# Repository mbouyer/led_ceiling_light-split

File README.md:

# led_ceiling_light-split

Plafonier à LEDs 12V pour bateau, avec 2 puissances (puissance réduite en navigation). Version en deux parties de led_ceiling_light

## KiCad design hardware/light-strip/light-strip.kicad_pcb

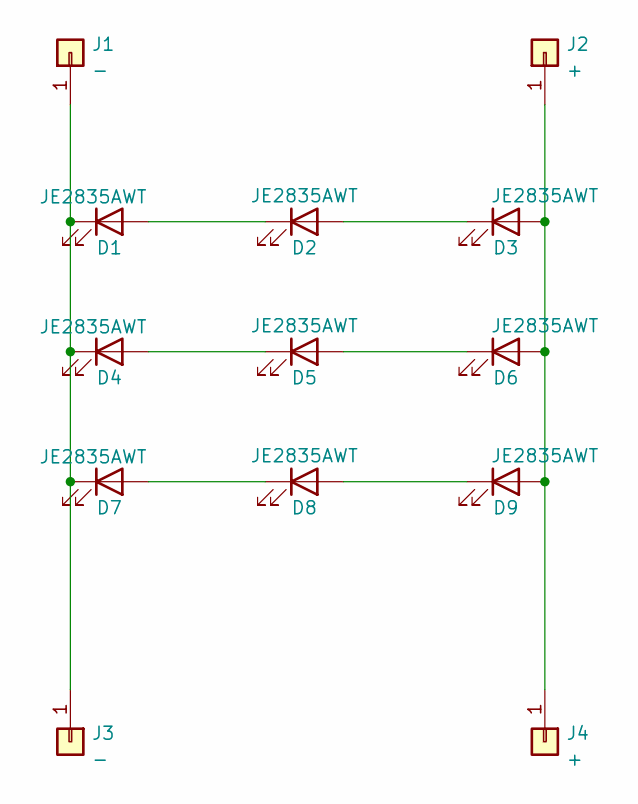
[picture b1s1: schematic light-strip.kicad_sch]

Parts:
D1, D2, D3, D4, D5, D6, D7, D8, D9: JE2835AWT; LED_PLCC_2835_Handsoldering
J1, J3: -; SolderWirePad_1x01_SMD_5x10mm
J2, J4: +; SolderWirePad_1x01_SMD_5x10mm

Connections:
unnamed: D1.1 (K), D4.1 (K), D7.1 (K), J1.1, J3.1
unnamed: D1.2 (A), D2.1 (K)
unnamed: D2.2 (A), D3.1 (K)
unnamed: D3.2 (A), D6.2 (A), D9.2 (A), J2.1, J4.1
unnamed: D4.2 (A), D5.1 (K)
unnamed: D5.2 (A), D6.1 (K)
unnamed: D7.2 (A), D8.1 (K)
unnamed: D8.2 (A), D9.1 (K)

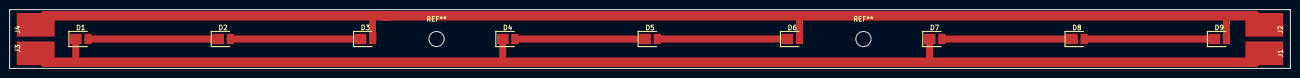
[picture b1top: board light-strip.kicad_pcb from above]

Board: 2 copper layers, 270.0 x 12.4 mm, 13 parts (0 on the bottom side), 8 nets.

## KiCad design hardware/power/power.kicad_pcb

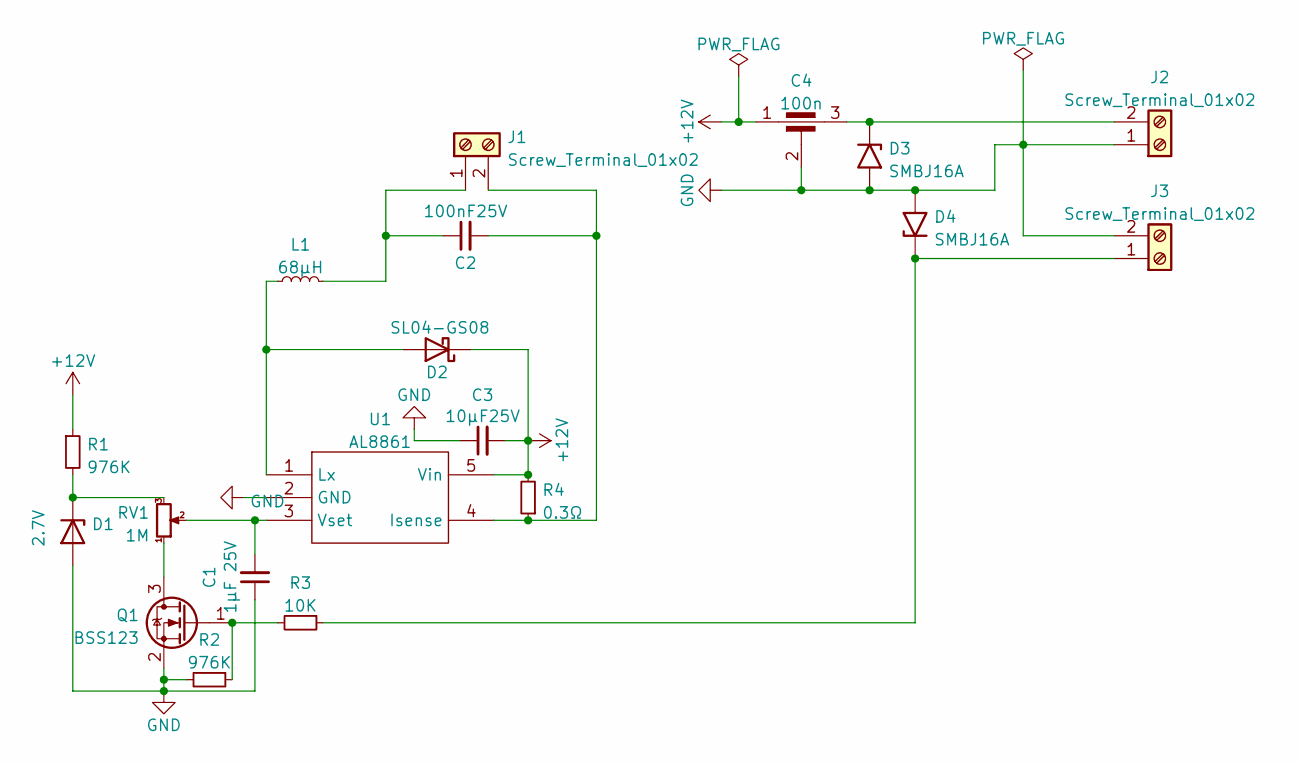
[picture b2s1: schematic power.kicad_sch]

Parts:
C1: 1µF 25V; C_0805_2012Metric_Pad1.18x1.45mm_HandSolder
C2: 100nF25V; C_0603_1608Metric_Pad1.08x0.95mm_HandSolder
C3: 10µF25V; C_1210_3225Metric_Pad1.33x2.70mm_HandSolder
C4: 100n; C_filter_0805
D1: 2.7V; D_MiniMELF_Handsoldering
D2: SL04-GS08; D_SMF
D3, D4: SMBJ16A; D_SMB_Handsoldering
J1, J2, J3: Screw_Terminal_01x02; amphenol_TZ02
L1: 68µH; L_Taiyo-Yuden_NR-80xx_HandSoldering
Q1: BSS123; SOT-23
R1, R2: 976K; R_0603_1608Metric_Pad0.98x0.95mm_HandSolder
R3: 10K; R_0805_2012Metric_Pad1.20x1.40mm_HandSolder
R4: 0.3Ω; R_1206_3216Metric_Pad1.30x1.75mm_HandSolder
RV1: 1M; Potentiometer_Piher_PT-10-V10_Vertical
U1: AL8861; TSOT-23-5_HandSoldering

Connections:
+12V: C3.2, C4.1, D2.1 (K), R1.1, R4.2, U1.5 (Vin)
GND: C1.1, C3.1, C4.2, D1.2 (A), D3.2 (A2), D4.2 (A2), J2.1, J3.2, Q1.2 (S), R2.2, U1.2 (GND)
unnamed: C1.2, RV1.2, U1.3 (Vset)
unnamed: C2.1, J1.1, L1.2
unnamed: C2.2, J1.2, R4.1, U1.4 (Isense)
unnamed: C4.3, D3.1 (A1), J2.2
unnamed: D1.1 (K), R1.2, RV1.3
unnamed: D2.2 (A), L1.1, U1.1 (Lx)
unnamed: D4.1 (A1), J3.1, R3.1
unnamed: Q1.1 (G), R2.1, R3.2
unnamed: Q1.3 (D), RV1.1

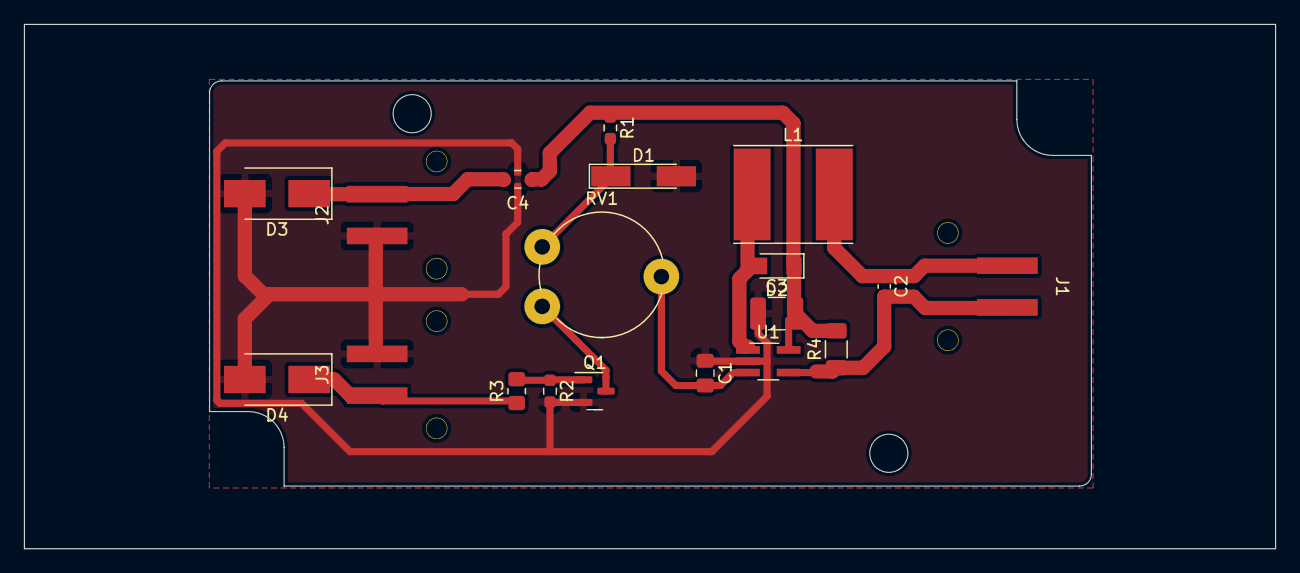
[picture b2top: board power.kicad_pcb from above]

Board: 2 copper layers, 105.0 x 44.0 mm, 19 parts (0 on the bottom side), 11 nets.

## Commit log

2023-02-24 Initial version of power and led strip
2023-03-31 change connectors for SMD ones
2023-03-31 Add fabrication files
2023-04-20 Add a second set of pad for symetrical connect Update PCB and ajust size with housing Add 2 mounting holes, just in case Add fabrication files.
2023-04-21 Add LED rail schematic
2023-04-23 Add 3d model for rail termination
2023-04-24 Add a hole for cable. Add stl file.
2023-04-25 Add a photo of project
2023-04-25 Update README.md
    Add photo
